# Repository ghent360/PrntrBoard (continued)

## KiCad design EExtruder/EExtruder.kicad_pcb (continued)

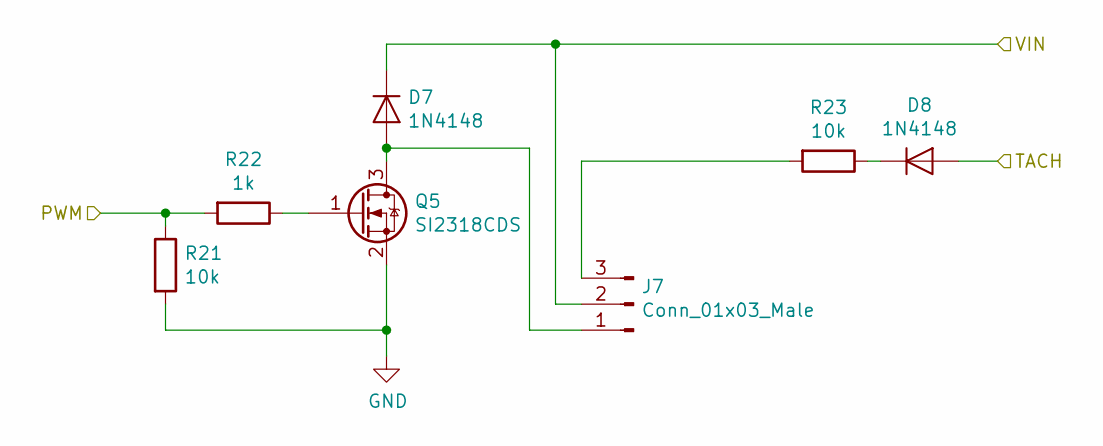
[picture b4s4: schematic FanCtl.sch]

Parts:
D7, D8: 1N4148; D_SOD-323_HandSoldering
J8: Conn_01x03_Male; PinHeader_1x03_P2.54mm_Vertical
Q5: SI2318CDS; SOT-23
R21, R23: 10k; R_0603_1608Metric
R22: 1k; R_0603_1608Metric

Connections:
/E0_FAN: R21.1, R22.2; also elsewhere on the board
/TACH_E0: D8.2 (A); also elsewhere on the board
/VIN: D7.1 (K), J8.2; also elsewhere on the board
GND: Q5.2 (S), R21.2; also elsewhere on the board
unnamed: D8.1 (K), R23.1
unnamed: Q5.1 (G), R22.1

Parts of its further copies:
D9, D10, D11, D12: 1N4148; D_SOD-323_HandSoldering
J7, J9: Conn_01x03_Male; PinHeader_1x03_P2.54mm_Vertical
Q6, Q7: SI2318CDS; SOT-23
R24, R26, R27, R29: 10k; R_0603_1608Metric
R25, R28: 1k; R_0603_1608Metric

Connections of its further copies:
/E1_FAN: R24.1, R25.2; also elsewhere on the board
/PWM0: R27.1, R28.2; also elsewhere on the board
/TACH0: D12.2 (A); also elsewhere on the board
/TACH_E1: D10.2 (A); also elsewhere on the board
/VIN: D9.1 (K), D11.1 (K), J7.2, J9.2; also elsewhere on the board
GND: Q6.2 (S), Q7.2 (S), R24.2, R27.2; also elsewhere on the board
unnamed: D10.1 (K), R26.1
unnamed: D11.2 (A), J9.1, Q7.3 (D)
unnamed: D12.1 (K), R29.1
unnamed: J9.3, R29.2
unnamed: Q6.1 (G), R25.1
unnamed: Q7.1 (G), R28.1

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
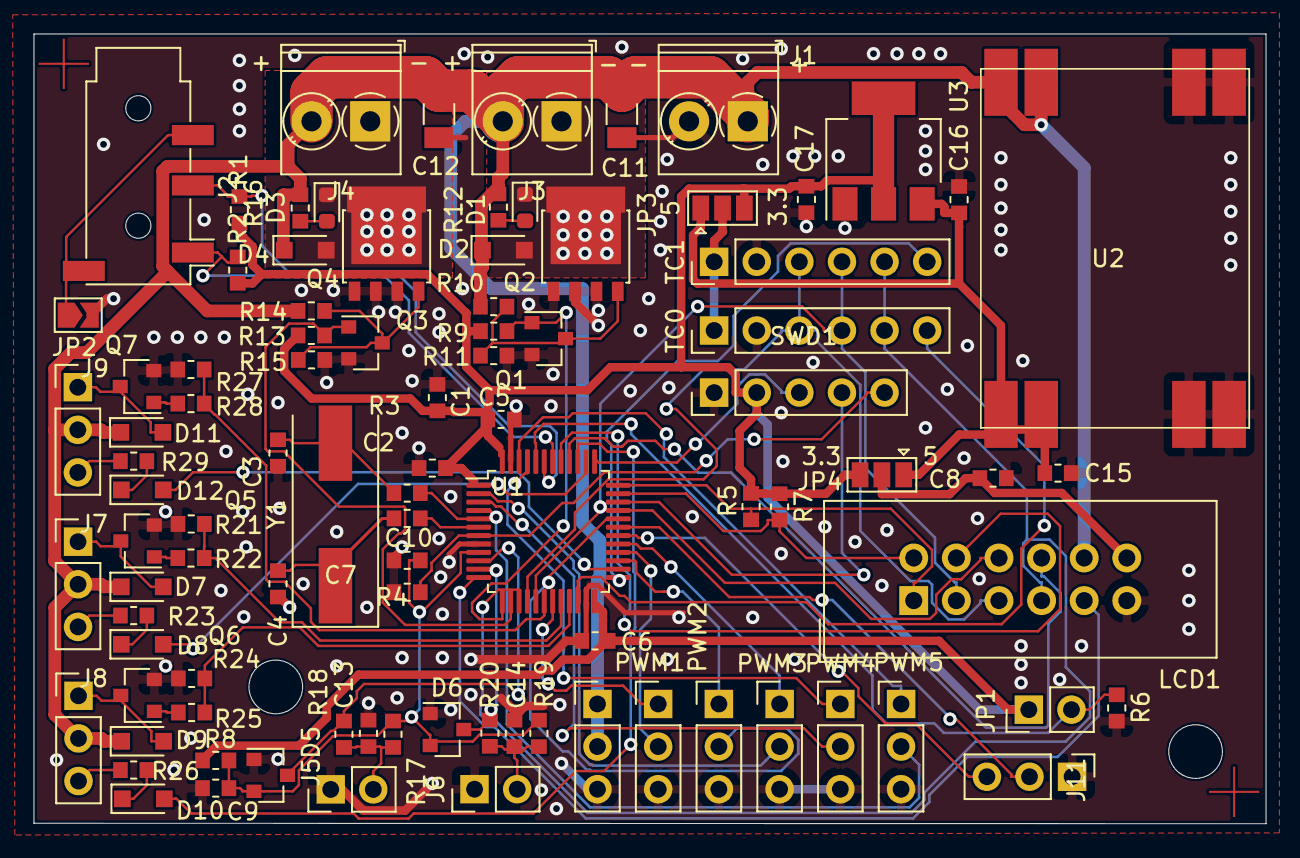
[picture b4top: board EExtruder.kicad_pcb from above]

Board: 2 copper layers, 73.4 x 47.1 mm, 97 parts (0 on the bottom side), 71 nets.

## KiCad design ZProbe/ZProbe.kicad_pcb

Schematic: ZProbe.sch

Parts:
C1: 0.01uF; C_0603_1608Metric
C2: 0.1uF; C_0603_1608Metric
D1: 1N4148; D_SOD-323_HandSoldering
J1: SENSOR; PinHeader_1x03_P2.54mm_Horizontal
J2: Vin; JST_EH_B02B-EH-A_1x02_P2.50mm_Vertical
J3: Z-Probe; PinHeader_1x04_P2.54mm_Horizontal
Q1: DTA124E; SOT-23
Q2: DTC124E; SOT-23
R1: 1k; R_0603_1608Metric
R2: 10k; R_0603_1608Metric

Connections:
+5V: C2.1, J3.4, Q1.3, R2.1
GND: C1.2, C2.2, J1.1, J2.2, J3.2, Q2.2
unnamed: C1.1, D1.1 (K), R1.1
unnamed: D1.2 (A), Q1.1
unnamed: J1.2, R1.2
unnamed: J1.3, J2.1
unnamed: J3.1, Q2.3, R2.2
unnamed: Q1.2, Q2.1

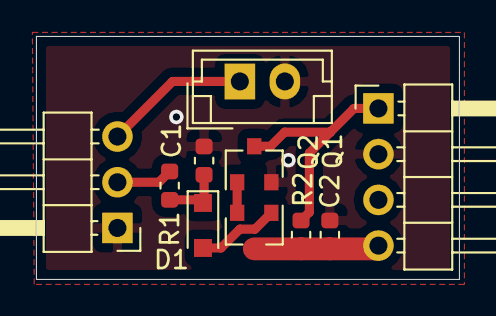
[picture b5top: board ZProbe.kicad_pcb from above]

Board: 2 copper layers, 23.5 x 13.5 mm, 10 parts (0 on the bottom side), 8 nets.

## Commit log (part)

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2018-03-26 Its a good start.
2018-03-26 Added extruder sheet (empty for now).
2018-03-26 Add 3 axis and 2 extruders. Basic thermistor temperature sensing and MOSFET heaters in the extruders.
2018-04-02 Finish the schematics. All pins are assinged to the NUCLEO-64 board.
2018-04-02 Added LICENSE file.
2018-04-05 Split the bed heater in separate schematics.
2018-04-06 Updated components. Removed power supply. Component layout on PCB.
2018-04-06 Add outline.
2018-04-08 First routing complete. DRC pass.
2018-04-08 Added mounting holes and fiducials. Placed all components labels so they are readable.
2018-04-08 Hmm price is too expencive for this board. Looking to reduce the specs to 6/6 mil spacing .3mm via drills.
2018-04-08 Placer all on 10x10 board. All labels are readable. Added connector text.
2018-04-08 Added V_MOTOR copper poors.
2018-04-08 Added drive power pours for the motor connections. Added vias to the outer poors.
2018-04-08 Complete the drivers power pours on layer 3.
2018-04-08 Routed some easy traces. 97 to go.
2018-04-08 Re-worked motor protection capacitors, so they don't take space from the copper pours for the driver output pins.
2018-04-09 Routed SPI common signals.
2018-04-09 All routed - first version success.
2018-04-09 Added image of the current V1 board.
2018-04-09 Added 3D model of the nucleo board. Created a few screenshots from the 3D viewer.
2018-04-10 Update schematics to use TMC5130/TMC2130 drivers.
2018-04-15 Added motor clock source.
2018-04-15 Some progress placing components.
2018-04-16 Moved labels around. All should be visible and readable. (for now).
2018-04-16 Started routing power.
2018-04-17 Routed power stage for extruders and heater controls. Routed some easy connections.
2018-04-17 Updated motor connector pinout.
2018-04-17 Route some moters power connectors.
2018-04-19 Locked vias.
2018-04-19 96 unrouted traces to go.
2018-04-19 Locked vias on power pads for the drivers.
2018-04-20 Routed some more traces. 27 to go.
2018-04-20 15 traces to go.
2018-04-20 All traces routed.
2018-04-20 Sprinkled vias, added labels, re-routed the motor power a bit.
2018-04-20 Add copper on L2 over the driver vias.
2018-04-20 Straighten come lines, re-route heater power. Add heater mosfet pours on the bottom layer.
2018-04-24 Change 10uF capacitor footprints to 1206.
2018-04-26 Update label locations, so there are no vias under the labels.
2018-05-04 Make the fiducials visible to the pos report.
2018-05-04 Movet top FID to the top right corner. Added PCB origin. Switched 0.1uF 50V cpas to 0402 size.
2018-05-09 Updated TR3 foor print and re-routed tracks.
2018-05-10 Added 10k pullups to control inputs for heaters, to disable heaters when control module is not installed.
2018-05-12 Adding a readme file.
2018-05-12 Update the readme file.
2018-05-12 Added readme file.
2018-05-12 Updated readme text.
2018-05-12 Updated readme.
2018-05-12 Fix spelling :-(
2018-05-13 Re-routed the extruder motor controls, so there is a large area on the bottom to disipate the IC heat.
2018-05-13 Remove more heat obstacles on the bottom plate.
2018-05-13 Re-route the axis extruder so the bottom plate has more space to dissipate heat.
2018-05-13 Added led on all power busses.
2018-05-14 Added LCD screen. Updated REDME.
2018-05-25 Position heater filter capacitors closer to the power bus.
2018-05-25 Fix small routing issues.
2018-05-28 Add gerber and drill files.
2018-05-28 Added dual themocouple pins. You'll have to sacrifice the controllable extruder cooling fans via jumpers.
2018-05-28 Updated the readme with the latest design mods.
2018-06-05 Generated front paste layer in DXF format.
2018-06-10 Initial component placement.
2018-06-11 Routed the two extruder motors power. Routed heat MOSFET power.
2018-06-11 Routed more signals 12 to go.
2018-06-13 Routing is complete.
2018-06-14 Increase thermal pads size for the drivers. Fix mosfet solder mask footprint.
2018-06-16 Added bottom solder mask.
2018-06-21 Clean README.md.
2018-06-21 Added filter capacitors on the 3.3v as well as the AVREF power inputs.
2018-06-23 Updated rev number in the silkscreen.
2018-06-23 Changed 1000pF capacitor value in teh motor drivers.
2018-06-24 Cleanup paths and library names.
2018-06-24 Add 3D models locally compresed.
2018-06-24 Ignore uncompressed 3D model files.
2018-06-24 Add more filtering caps.
2018-06-24 Cherry pick path name changes.
2018-06-30 Started new layout.
2018-07-02 Fix endstops.
2018-07-02 Update PCB from schematics.
2018-07-03 Updated redme.
2018-07-04 Fix endstops. Add extra fan connectors. Start routing motors drivers.
2018-07-09 Routed all motor driver power traces.
2018-07-09 59 traces to go.
2018-07-10 39 Traces to go.
2018-07-11 Cleanup. Generated gerbers.
2018-07-11 Update back labels.
2018-07-13 Improve layout. Update footprints, reposition labels. Update FID* to a cross.
2018-07-15 Minor improvements to the layout - leave more clearance around the motor connectors.
2018-07-15 Update readme.
2018-07-20 Added heatsink labels on the bottom. Moved electrolytic caps around to make more clearance for top heatsink(s). Moved extra fan connectors around. Increased VIA spacing on driver bus connectors. Fixe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
2018-07-21 Relocate filter cap next to E1. Change z-probe input resistor value.
2018-07-21 Polish the gerbers.
2018-07-21 Update ZProbe PCB labels. Make new gerbers.
2018-07-21 Generate gerbers to JLPCB recomended naming.
2018-07-21 Enhance the motor driver output signal copper zones.
2018-07-24 Add new FID footprint.
2018-07-24 Update FID footprint.
2018-07-24 Update rev label.
2018-07-24 Add STM32F407RE dev kit symbol.
2018-07-28 Re-generate output files.
2018-07-31 Update libraries. Board revision.
2018-07-31 Started rev 3. Added encoder iand button input. Re-routed LCD A0 and RESET to be connected to the HW I2C pins.
2018-07-31 Updated readme for the rev3 board.
2018-08-01 Improve 5V plane.
2018-08-05 Add thermal releaf on most truehole connectors.
2018-08-05 Update some signal traces to wiggle less.
2018-08-05 Add more temp files to the gitignore
2018-08-05 Update 3D models for the connectors. Remove the nucleo-64 3D model fron the pcb file - it was loading very slow. Generate board 3D model.
2018-08-12 Switch away from rounded rect pads. The PCB boar house had issues making the board.
2018-08-19 Move power labels on the mask close to the edge.
2018-09-02 Regenerate plit files. Minor trace movements.
2018-10-11 Add external extruder control board prototype.
2018-10-11 Component layout complete.
2018-10-13 Unrouted - only power.
2018-10-14 All routed - thank you autorouter.
2018-10-14 Select correct terminals. Use old style square footprints.
2018-10-14 Add solder jumper on the audio jack to avoid ground loops.
2018-10-14 Generate gerber files.
2018-10-14 Add fiducials.
2018-10-15 Add "lite" version schematics.
2018-11-12 Update readme with pointer to the Smoothie port.
2018-11-19 Updated status.
2018-11-23 Add custom NUCLEO-64 replacement based on F407VE.
2018-11-25 Ordered rev1 of the Nucleo-64 board.
2018-12-05 Make the NUCLEO-64-F407 board with rounded corners.
2018-12-09 Updated EExtruder ground routing. Renamed Nucleo-64 LED values.
2018-12-24 Updated current status.
2019-01-13 Added 3.3V LDO, updated TC connectors to 6 pins. Re-arranged the layout.
2019-01-13 Update to rev3.
2019-01-13 Update ground plane. Power to MOSFETS. Heatpads for MOSFETS.
2019-01-13 Added a few more vias.
2019-01-19 Updated .gitignore filter.
2019-01-20 Update annotations.
2019-01-20 Add missing files from the TMC2130 branch.
2019-01-20 Reset schematics for tmc2660. Clean the board layout.
2019-01-20 Placed power components.
2019-01-20 Only 5 traces to go.
2019-01-20 Add traces routed. Hooray!!!
2019-01-20 Completed. Added labels, small tweaks. Ready for fabrication.
2019-01-21 Hide all component reference names.
2019-01-21 Added OSHW logo.
2019-01-21 Update label location.
2019-01-21 Re-generated manufacturing files. Sent to fab.
2019-01-21 Increment revision number.
2019-01-26 Replicated outer power pads.
2019-01-26 Replicate inner pads. Unrouted all moror input voltage.
2019-01-26 Connect motor driver voltage. Copy power pad vias.
2019-01-27 Fix capavitor value.
2019-01-27 Updated traces for fan connectors.
2019-01-28 Add round edges.
2019-02-03 Rename LED values.
2019-02-03 Updated component values, updated component footprint.
2019-04-08 Switched nuc-f407 to rev 3.
2019-04-14 Add two fuses.
2019-04-14 Added model for the Fuses.
2019-04-15 Make better power routing to the fuses.
2019-04-15 Added reverse polarity input protection diodes. Re-routed input power.
2019-04-15 Switch http to https link to blog
2019-04-27 Updated EExtruder connector 3d models.
2019-04-28 Update power connector to 30A rated one.
2019-05-12 Update thermistor filter capacitor values.
2019-05-12 Fix bugs when upgrading KiCAD versions.
2019-05-19 Move power LEDs positions.
2019-05-19 Move E1 label.
2019-05-19 Added clock source for the TMC2660 drivers.
2019-05-20 Moved some labels to make them more readable.
2019-05-24 Improve power pin traces to VSA and VSB pins on the motor drivers.
2019-05-25 Update fuxe foorprint to 2410 holders.
2019-05-25 Update 3D model for fuses, move labels around.
2019-05-25 Updated power connector. Moved aux power pins.
2019-05-26 Updated motor connectors to Molex SL style.
2019-05-26 Update 2660 screenshot.
2019-06-09 Remove reverse voltage protection diodes. Test was not successful. Re-aranged the heater LEDs and some
2019-06-14 Update ground routing for the MCU.
2019-06-14 Update bottom silk screen. Ordered R4.
2019-06-14 Updare working rev to rev 5.
2019-06-23 Update a few footprints so the origin of the footpring is in teh center.
2019-06-23 Renamed Button so it does not contain space in teh anme.
2019-06-24 Fixed incorrect footprint attribute.
2019-07-05 Updated 3d models, to the ones I actually use.
2019-07-05 Add missing footprint file.
2019-07-15 Move aux power connectors out of the wau. Update fuse footprints.
2019-07-19 Add reverse polarity protection diode.
2019-07-20 Updated to rev6.
2019-07-25 Wired most of the schematics for 2209 drivers.
2019-07-26 Finished the schematics wiring and reset the routing.
2019-07-27 Router X and Y drivers (preliminary).
2019-07-27 Routed all driver power zones.
2019-07-27 Added pul-ups on the UART ports and series resistors for protection.
2019-07-31 Routed heater components and fan connectors and drivers.
2019-08-17 Placed all components on the board.
2019-08-18 Fix R22 net assignement.
2019-08-18 Fixed ground connections to motor driver pins. Routec 3.3V to drivers.
2019-08-18 Routed some of the Z driver pins.
2019-08-18 114 unrouted connections left.
2019-08-18 100 unrouted wires left.
2019-08-18 Hide component references and values.
2019-08-18 65 unrouted wires to go.
2019-08-18 54 unrouted wires to go.
2019-08-18 34 unrouted wires to go.
2019-08-18 27 unrouted wires to go.
2019-08-18 14 unrouted wires to go.
2019-08-18 All wires routed. Addes F silk text.
2019-08-18 Add B Silk text.
2019-08-19 Re routed some traces.
2019-08-21 Update to rev 2.
2019-08-21 Added extra fuse for the extruder heaters.
2019-08-24 Fixed typo
2019-08-25 Add kicad image.
2019-08-26 Minor updates to the nucleo-64 board. Added more signals to the extension headers. Use resistor networks. Fix diode footprint.
2019-08-27 Add 3rd fuse. Fix the layout.
2019-08-27 Still on rev6.
2019-08-29 Add RGB leds to IO pins.
2019-08-29 Started rev 7. Moved cap out put th eair flow way.
2019-08-31 Add LCD io board.
2019-09-02 Moved Z-Prove avain from endsto LEDs. Mozed some silk screen labels around.
2019-09-02 Add reverse power protection to the nucleo board.
2019-10-21 Move labels so they are readable.
2019-10-31 Add tracker.
2019-10-31 Remove tracker.
2019-11-07 Updated README.md.
2020-05-02 Fix bug in the TMC2130 driver schematics.
